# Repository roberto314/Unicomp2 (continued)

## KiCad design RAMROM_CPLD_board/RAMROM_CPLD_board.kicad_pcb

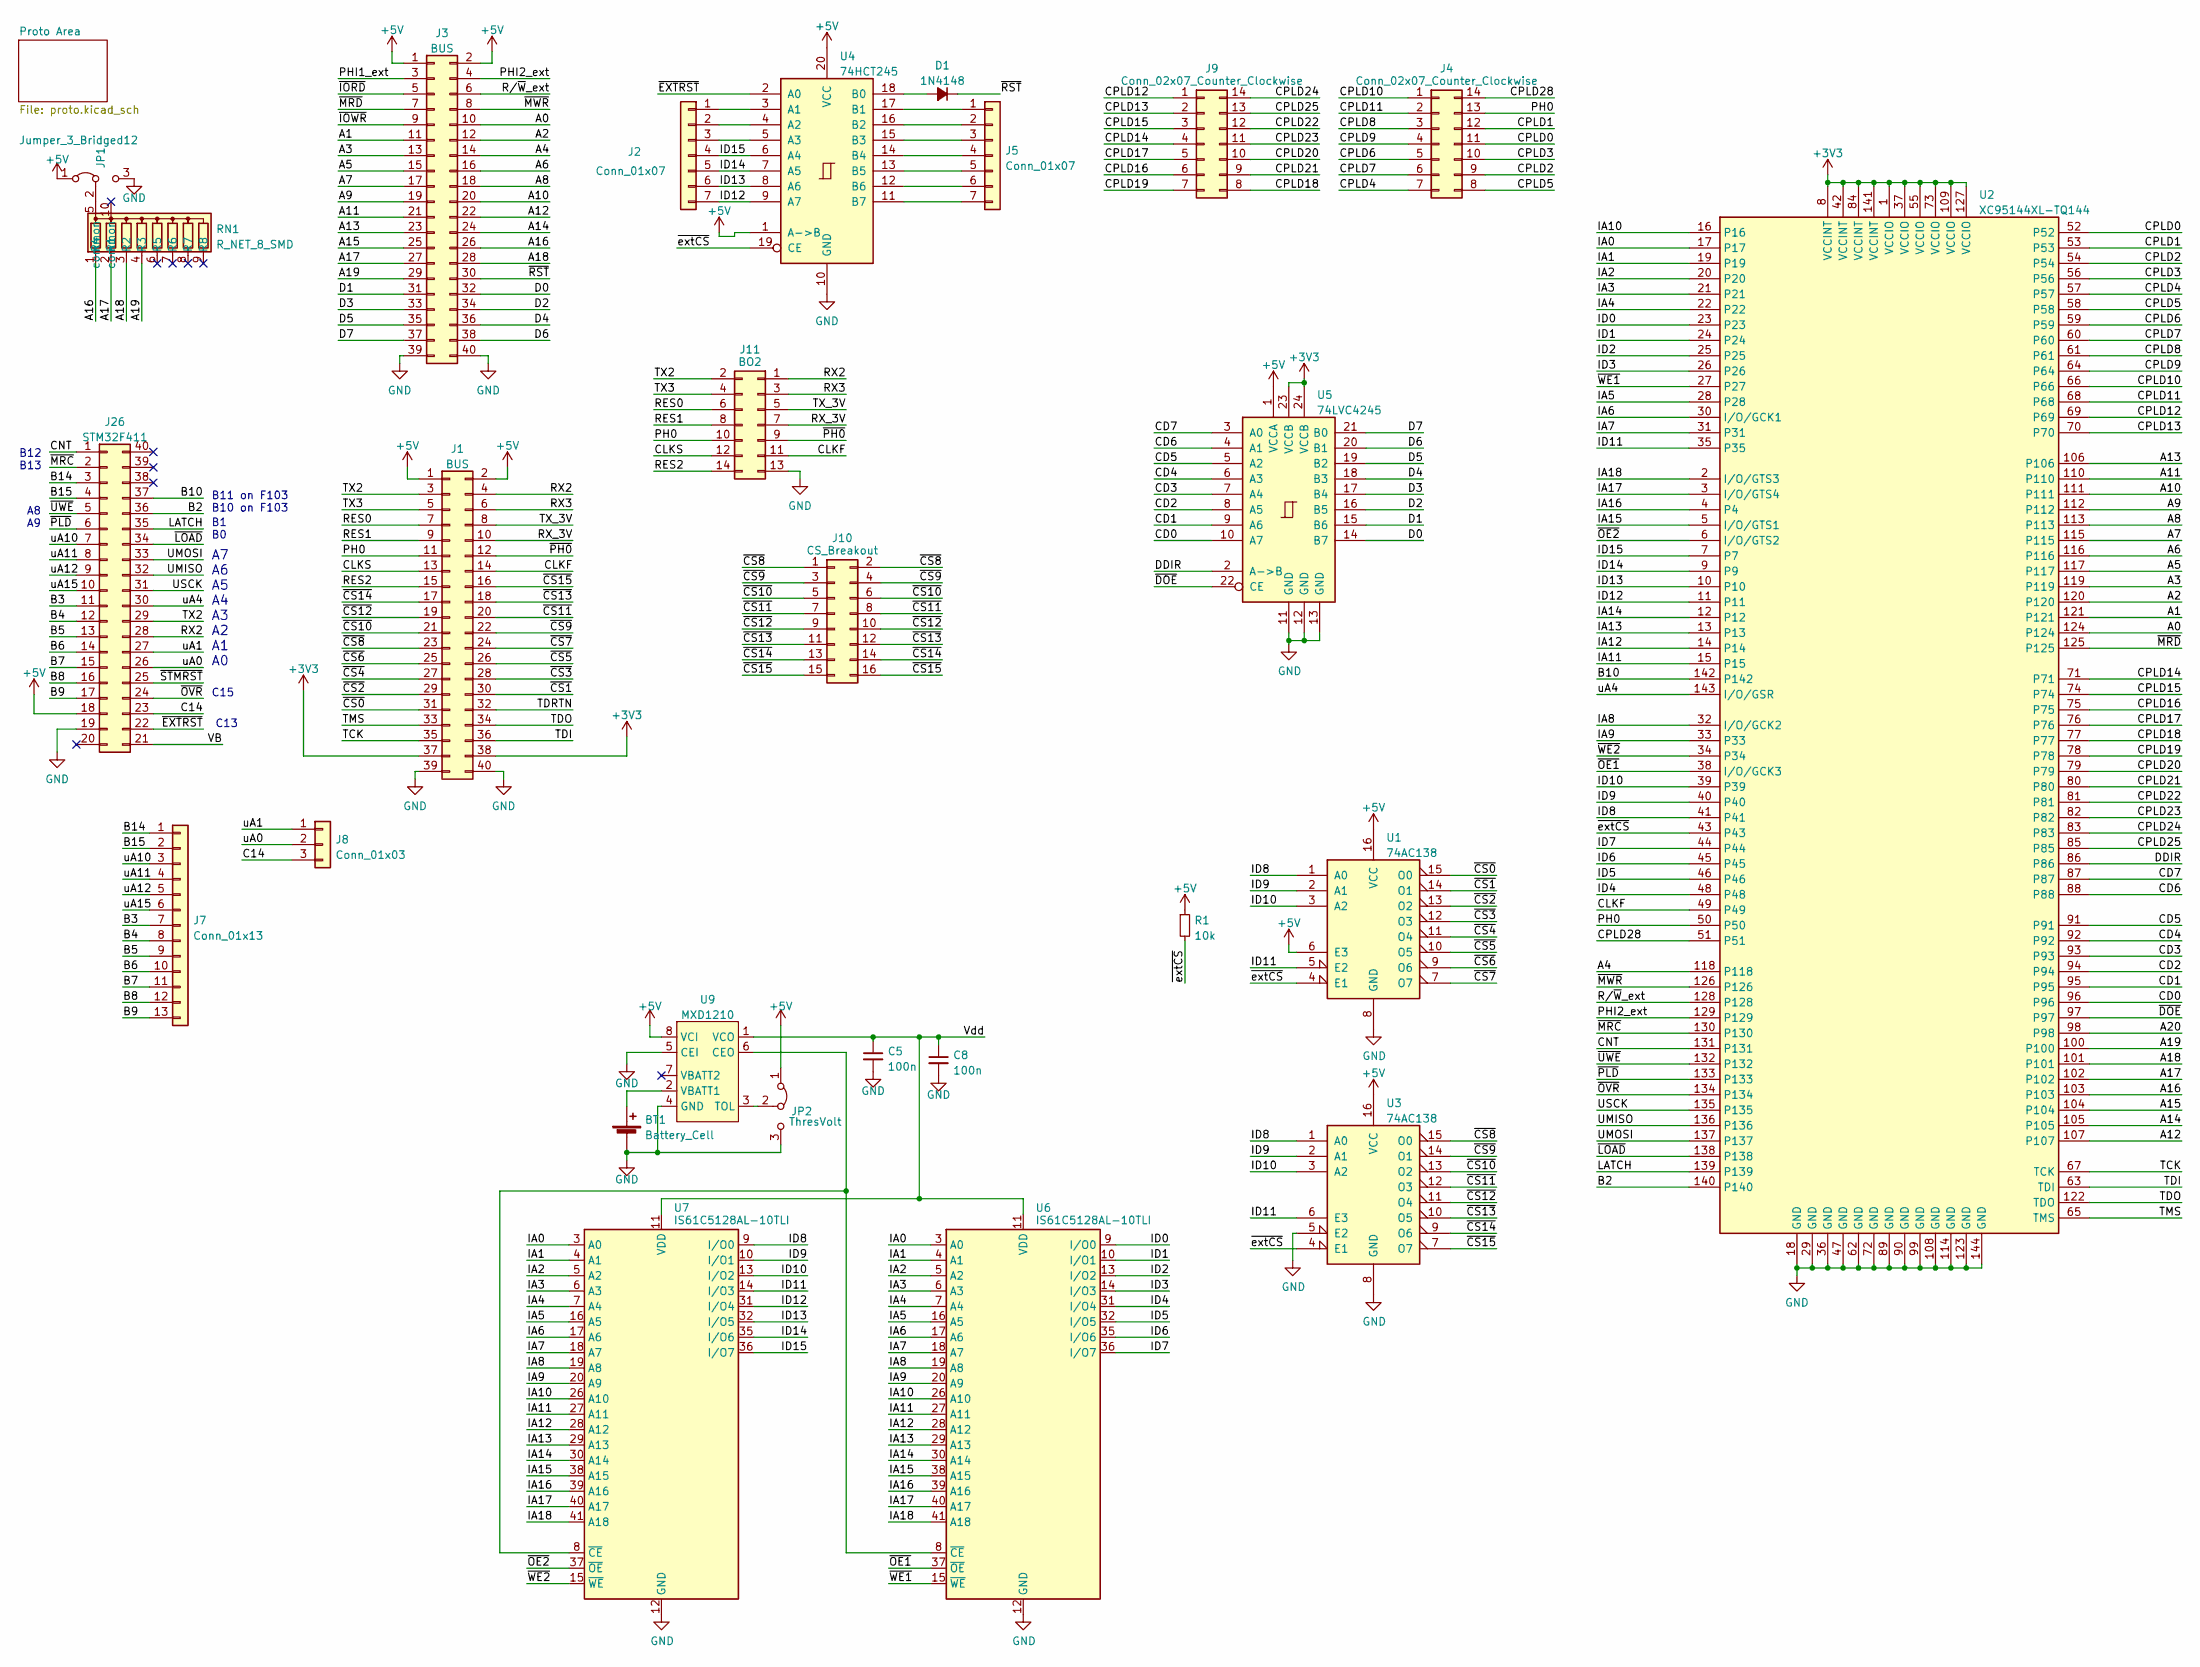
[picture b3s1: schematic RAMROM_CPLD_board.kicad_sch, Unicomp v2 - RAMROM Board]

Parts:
BT1: Battery_Cell; BatteryHolder_Keystone_103_1x20mm
C5, C8: 100n; C_1206_3216Metric
D1: 1N4148; D_1206_3216Metric_Pad1.42x1.75mm_HandSolder
J1, J3: BUS; PinSocket_2x20_P2.54mm_Vertical
J2, J5: Conn_01x07; PinHeader_1x07_P2.54mm_Vertical
J4, J9: Conn_02x07_Counter_Clockwise; PinHeader_2x07_P2.00mm_Vertical
J7: Conn_01x13; PinHeader_1x13_P2.54mm_Vertical
J8: Conn_01x03; PinHeader_1x03_P2.00mm_Vertical
J10: CS_Breakout; PinHeader_2x08_P2.00mm_Vertical
J11: BO2; PinHeader_2x07_P2.54mm_Vertical
J26: STM32F411; DIP-40_W15.24mm_Socket_LongPads
JP1: Jumper_3_Bridged12; SolderJumper-3_P1.3mm_Bridged12_RoundedPad1.0x1.5mm_NumberL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
JP2: ThresVolt; SolderJumper-3_P1.3mm_Bridged12_RoundedPad1.0x1.5mm_NumberL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
R1: 10k; R_1206_3216Metric
RN1: R_NET_8_SMD; R_Net2512_6.4x3.1_P1.27
U1, U3: 74AC138; TSSOP-16_4.4x5mm_P0.65mm
U2: XC95144XL-TQ144; TQFP-144_20x20mm_P0.5mm
U4: 74HCT245; DIP-20_W7.62mm_Socket_LongPads
U5: 74LVC4245; TSSOP-24_4.4x7.8mm_P0.65mm
U6, U7: IS61C5128AL-10TLI; TSOP-II-44_10.16x18.41mm_P0.8mm
U9: MXD1210; SOP-8_3.9x4.9mm_P1.27mm

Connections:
+3V3: J1.37, J1.38, U2.1 (VCCIO), U2.8 (VCCINT), U2.37 (VCCIO), U2.42 (VCCINT), U2.55 (VCCIO), U2.73 (VCCIO), U2.84 (VCCINT), U2.109 (VCCIO), U2.127 (VCCIO), U2.141 (VCCINT), U5.23 (VCCB), U5.24 (VCCB); also elsewhere on the board
+5V: J1.1, J1.2, J3.1, J3.2, J26.18, JP1.1 (A), JP2.1 (A), R1.1, U1.6 (E3), U1.16 (VCC), U3.16 (VCC), U4.1 (A->B), U4.20 (VCC), U5.1 (VCCA), U9.8 (VCI); also elsewhere on the board
/A0: J3.10, U2.124
/A1: J3.11, U2.121
/A2: J3.12, U2.120
/A3: J3.13, U2.119
/A4: J3.14, U2.118
/A5: J3.15, U2.117
/A6: J3.16, U2.116
/A7: J3.17, U2.115
/A8: J3.18, U2.113
/A9: J3.19, U2.112
/A10: J3.20, U2.111
/A11: J3.21, U2.110
/A12: J3.22, U2.107
/A13: J3.23, U2.106
/A14: J3.24, U2.105
/A15: J3.25, U2.104
/A16: J3.26, RN1.1 (R4), U2.103
/A17: J3.27, RN1.2 (R1), U2.102
/A18: J3.28, RN1.3 (R2), U2.101
/A19: J3.29, RN1.4 (R3), U2.100
/A20: U2.98
/B2: J26.36, U2.140
/B3: J7.7, J26.11
/B4: J7.8, J26.12
/B5: J7.9, J26.13
/B6: J7.10, J26.14
/B7: J7.11, J26.15
/B8: J7.12, J26.16
/B9: J7.13, J26.17
/B10: J26.37, U2.142
/B14: J7.1, J26.3
/B15: J7.2, J26.4
/C14: J8.3, J26.23
/CD0: U2.96, U5.10 (A7)
/CD1: U2.95, U5.9 (A6)
/CD2: U2.94, U5.8 (A5)
/CD3: U2.93, U5.7 (A4)
/CD4: U2.92, U5.6 (A3)
/CD5: U2.91, U5.5 (A2)
/CD6: U2.88, U5.4 (A1)
/CD7: U2.87, U5.3 (A0)
/CLKF: J1.14, J11.11, U2.49
/CLKS: J1.13, J11.12
/CNT: J26.1, U2.131
/CPLD0: J4.11, U2.52
/CPLD1: J4.12, U2.53
/CPLD2: J4.9, U2.54
/CPLD3: J4.10, U2.56
/CPLD4: J4.7, U2.57
/CPLD5: J4.8, U2.58
/CPLD6: J4.5, U2.59
/CPLD7: J4.6, U2.60
/CPLD8: J4.3, U2.61
/CPLD9: J4.4, U2.64
/CPLD10: J4.1, U2.66
/CPLD11: J4.2, U2.68
/CPLD12: J9.1, U2.69
/CPLD13: J9.2, U2.70
/CPLD14: J9.4, U2.71
/CPLD15: J9.3, U2.74
/CPLD16: J9.6, U2.75
/CPLD17: J9.5, U2.76
/CPLD18: J9.8, U2.77
/CPLD19: J9.7, U2.78
/CPLD20: J9.10, U2.79
/CPLD21: J9.9, U2.80
/CPLD22: J9.12, U2.81
/CPLD23: J9.11, U2.82
/CPLD24: J9.14, U2.83
/CPLD25: J9.13, U2.85
/CPLD28: J4.14, U2.51
/D0: J3.32, U5.14 (B7)
/D1: J3.31, U5.15 (B6)
/D2: J3.34, U5.16 (B5)
/D3: J3.33, U5.17 (B4)
/D4: J3.36, U5.18 (B3)
/D5: J3.35, U5.19 (B2)
/D6: J3.38, U5.20 (B1)
/D7: J3.37, U5.21 (B0)
/DDIR: U2.86, U5.2 (A->B)
/IA0: U2.17, U6.3 (A0), U7.3 (A0)
/IA1: U2.19, U6.4 (A1), U7.4 (A1)
/IA2: U2.20, U6.5 (A2), U7.5 (A2)
/IA3: U2.21, U6.6 (A3), U7.6 (A3)
/IA4: U2.22, U6.7 (A4), U7.7 (A4)
/IA5: U2.28, U6.16 (A5), U7.16 (A5)
/IA6: U2.30 (I/O/GCK1), U6.17 (A6), U7.17 (A6)
/IA7: U2.31, U6.18 (A7), U7.18 (A7)
/IA8: U2.32 (I/O/GCK2), U6.19 (A8), U7.19 (A8)
/IA9: U2.33, U6.20 (A9), U7.20 (A9)
/IA10: U2.16, U6.26 (A10), U7.26 (A10)
/IA11: U2.15, U6.27 (A11), U7.27 (A11)
/IA12: U2.14, U6.28 (A12), U7.28 (A12)
/IA13: U2.13, U6.29 (A13), U7.29 (A13)
/IA14: U2.12, U6.30 (A14), U7.30 (A14)
/IA15: U2.5 (I/O/GTS1), U6.38 (A15), U7.38 (A15)
/IA16: U2.4, U6.39 (A16), U7.39 (A16)
/IA17: U2.3 (I/O/GTS4), U6.40 (A17), U7.40 (A17)
/IA18: U2.2 (I/O/GTS3), U6.41 (A18), U7.41 (A18)
/ID0: U2.23, U6.9 (I/O0)
/ID1: U2.24, U6.10 (I/O1)
/ID2: U2.25, U6.13 (I/O2)
/ID3: U2.26, U6.14 (I/O3)
/ID4: U2.48, U6.31 (I/O4)
/ID5: U2.46, U6.32 (I/O5)
/ID6: U2.45, U6.35 (I/O6)
/ID7: U2.44, U6.36 (I/O7)
/ID8: U1.1 (A0), U2.41, U3.1 (A0), U7.9 (I/O0)
/ID9: U1.2 (A1), U2.40, U3.2 (A1), U7.10 (I/O1)
/ID10: U1.3 (A2), U2.39, U3.3 (A2), U7.13 (I/O2)
/ID11: U1.5 (E2), U2.35, U3.6 (E3), U7.14 (I/O3)
/ID12: J2.7, U2.11, U4.9 (A7), U7.31 (I/O4)
/ID13: J2.6, U2.10, U4.8 (A6), U7.32 (I/O5)
/ID14: J2.5, U2.9, U4.7 (A5), U7.35 (I/O6)
/ID15: J2.4, U2.7, U4.6 (A4), U7.36 (I/O7)
/LATCH: J26.35, U2.139
/PH0: J1.11, J4.13, J11.10, U2.50
/PHI1_ext: J3.3
/PHI2_ext: J3.4, U2.129
/RES0: J1.7, J11.6
/RES1: J1.9, J11.8
/RES2: J1.15, J11.14
/RX2: J1.4, J11.1, J26.28
/RX3: J1.6, J11.3
/RX_3V: J1.10, J11.7
/R/~W_ext: J3.6, U2.128
/TCK: J1.35, U2.67 (TCK)
/TDI: J1.36, U2.63 (TDI)
/TDO: J1.34, U2.122 (TDO)
/TDRTN: J1.32
/TMS: J1.33, U2.65 (TMS)
/TX2: J1.3, J11.2, J26.29
/TX3: J1.5, J11.4
/TX_3V: J1.8, J11.5
/UMISO: J26.32, U2.136
/UMOSI: J26.33, U2.137
/USCK: J26.31, U2.135
/VB: J26.21
/Vdd: C5.1, C8.1, U6.11 (VDD), U6.33 (VDD), U7.11 (VDD), U7.33 (VDD), U9.1 (VCO)
/uA0: J8.2, J26.26
/uA1: J8.1, J26.27
/uA4: J26.30, U2.143 (I/O/GSR)
/uA10: J7.3, J26.7
/uA11: J7.4, J26.8
/uA12: J7.5, J26.9
/uA15: J7.6, J26.10
/~CS0: J1.31, U1.15 (O0)
/~CS1: J1.30, U1.14 (O1)
/~CS2: J1.29, U1.13 (O2)
/~CS3: J1.28, U1.12 (O3)
/~CS4: J1.27, U1.11 (O4)
/~CS5: J1.26, U1.10 (O5)
/~CS6: J1.25, U1.9 (O6)
/~CS7: J1.24, U1.7 (O7)
/~CS8: J1.23, J10.1, J10.2, U3.15 (O0)
/~CS9: J1.22, J10.3, J10.4, U3.14 (O1)
/~CS10: J1.21, J10.5, J10.6, U3.13 (O2)
/~CS11: J1.20, J10.7, J10.8, U3.12 (O3)
/~CS12: J1.19, J10.9, J10.10, U3.11 (O4)
/~CS13: J1.18, J10.11, J10.12, U3.10 (O5)
/~CS14: J1.17, J10.13, J10.14, U3.9 (O6)
/~CS15: J1.16, J10.15, J10.16, U3.7 (O7)
/~DOE: U2.97, U5.22 (CE)
/~EXTRST: J26.22, U4.2 (A0)
/~IORD: J3.5
/~IOWR: J3.9
/~LOAD: J26.34, U2.138
/~MRC: J26.2, U2.130
/~MRD: J3.7, U2.125
/~MWR: J3.8, U2.126
/~OE1: U2.38 (I/O/GCK3), U6.37 (~OE)
/~OE2: U2.6 (I/O/GTS2), U7.37 (~OE)
/~OVR: J26.24, U2.134
/~PH0: J1.12, J11.9
/~PLD: J26.6, U2.133
/~RST: D1.1 (K), J3.30
/~STMRST: J26.25
/~UWE: J26.5, U2.132
/~WE1: U2.27, U6.15 (~WE)
/~WE2: U2.34, U7.15 (~WE)
/~extCS: R1.2, U1.4 (E1), U2.43, U3.4 (E1), U4.19 (CE)
GND: BT1.2 (-), C5.2, C8.2, J1.39, J1.40, J3.39, J3.40, J11.13, J26.19, JP1.3 (B), JP2.3 (B), U1.8 (GND), U2.18 (GND), U2.29 (GND), U2.36 (GND), U2.47 (GND), U2.62 (GND), U2.72 (GND), U2.89 (GND), U2.90 (GND), U2.99 (GND), U2.108 (GND), U2.114 (GND), U2.123 (GND), U2.144 (GND), U3.5 (E2), U3.8 (GND), U4.10 (GND), U5.11 (GND), U5.12 (GND), U5.13 (GND), U6.12 (GND), U6.34 (GND), U7.12 (GND), U7.34 (GND), U9.4 (GND), U9.5 (CEI); also elsewhere on the board
unnamed: BT1.1 (+), U9.2 (VBATT1)
unnamed: D1.2 (A), U4.18 (B0)
unnamed: J2.1, U4.3 (A1)
unnamed: J2.2, U4.4 (A2)
unnamed: J2.3, U4.5 (A3)
unnamed: J5.1, U4.17 (B1)
unnamed: J5.2, U4.16 (B2)
unnamed: J5.3, U4.15 (B3)
unnamed: J5.4, U4.14 (B4)
unnamed: J5.5, U4.13 (B5)
unnamed: J5.6, U4.12 (B6)
unnamed: J5.7, U4.11 (B7)
unnamed: JP1.2 (C), RN1.5 (common)
unnamed: JP2.2 (C), U9.3 (TOL)
unnamed: U6.8 (~CE), U7.8 (~CE), U9.6 (CEO)

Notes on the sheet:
C13
B11 on F103 B10 on F103
B12 B13
C15
A7 A6 A5 A4 A3 A2 A1 A0
B1 B0
A8 A9

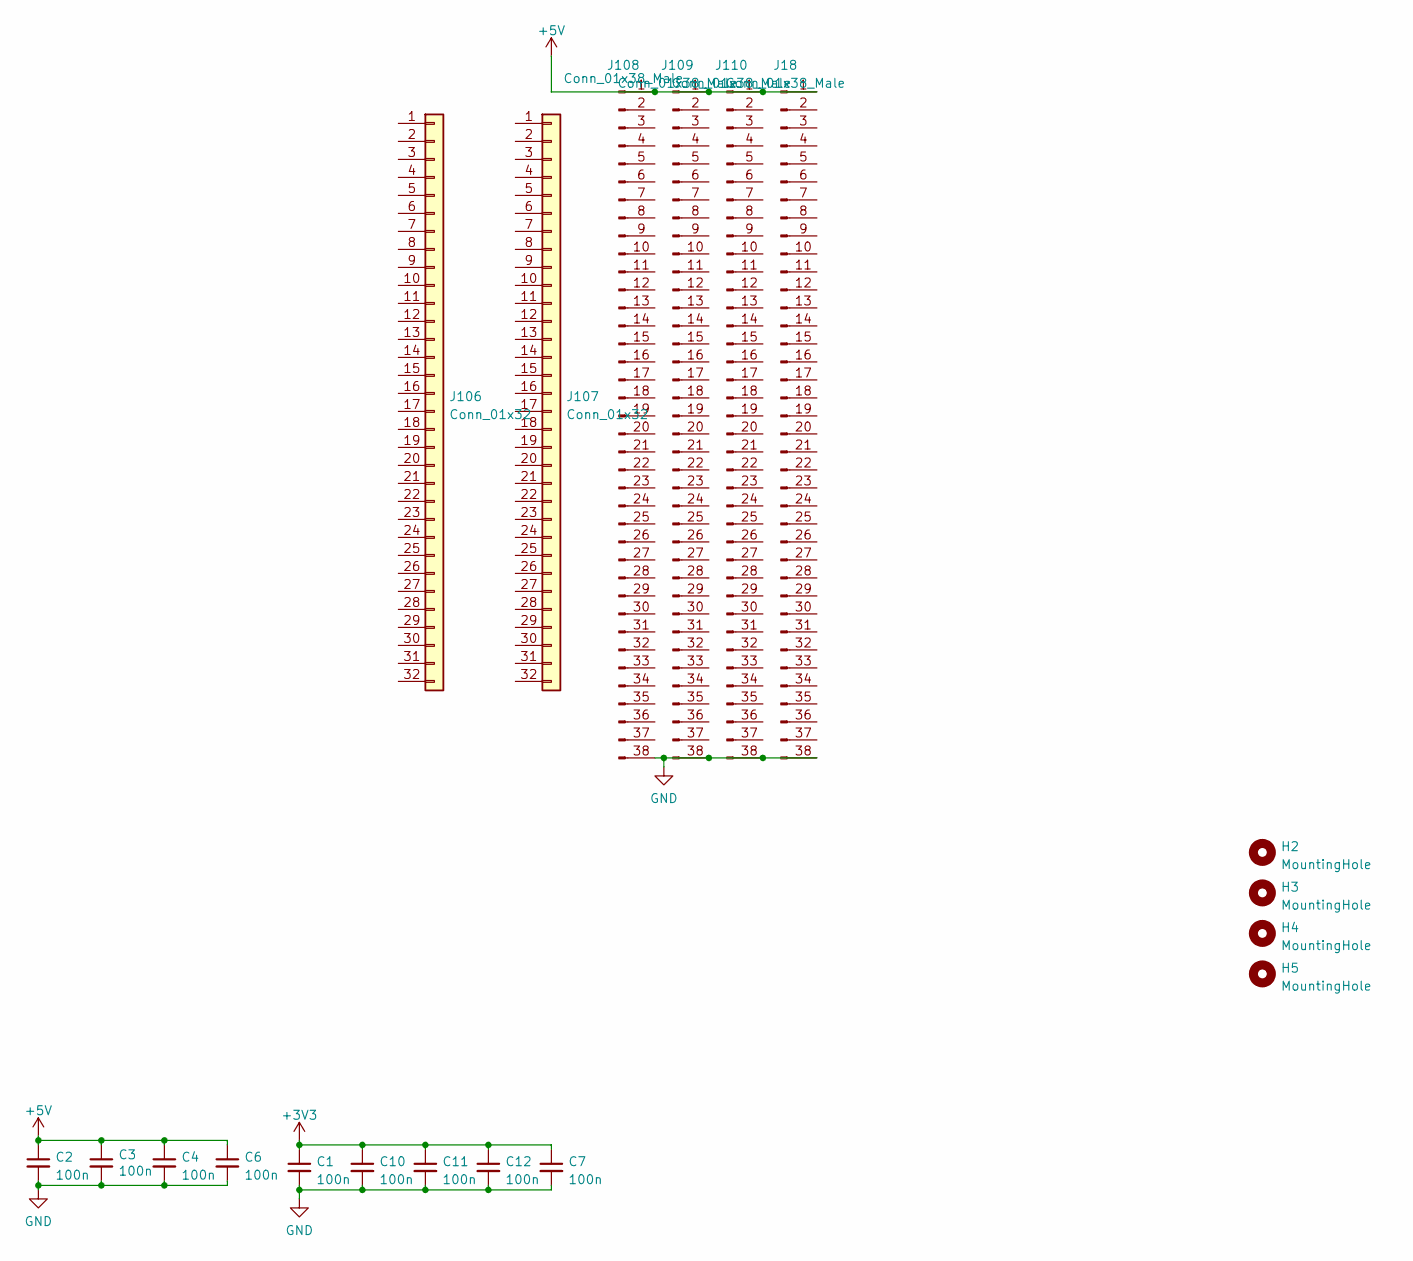
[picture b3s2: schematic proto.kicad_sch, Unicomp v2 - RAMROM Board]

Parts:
C1, C2, C4, C6, C7, C10, C11, C12: 100n; C_1206_3216Metric
C3: 100n; C_1206_3216Metric_Pad1.33x1.80mm_HandSolder
H2, H3, H4, H5: MountingHole; MountingHole_3.2mm_M3
J18, J108, J109, J110: Conn_01x38_Male; PinHeader_1x38_P2.54mm_Vertical
J106, J107: Conn_01x32; PinHeader_1x32_P2.54mm_Vertical

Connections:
+3V3: C1.1, C7.1, C10.1, C11.1, C12.1; also elsewhere on the board
+5V: C2.1, C3.1, C4.1, C6.1, J18.1, J108.1, J109.1, J110.1; also elsewhere on the board
GND: C1.2, C2.2, C3.2, C4.2, C6.2, C7.2, C10.2, C11.2, C12.2, J18.38, J108.38, J109.38, J110.38; also elsewhere on the board

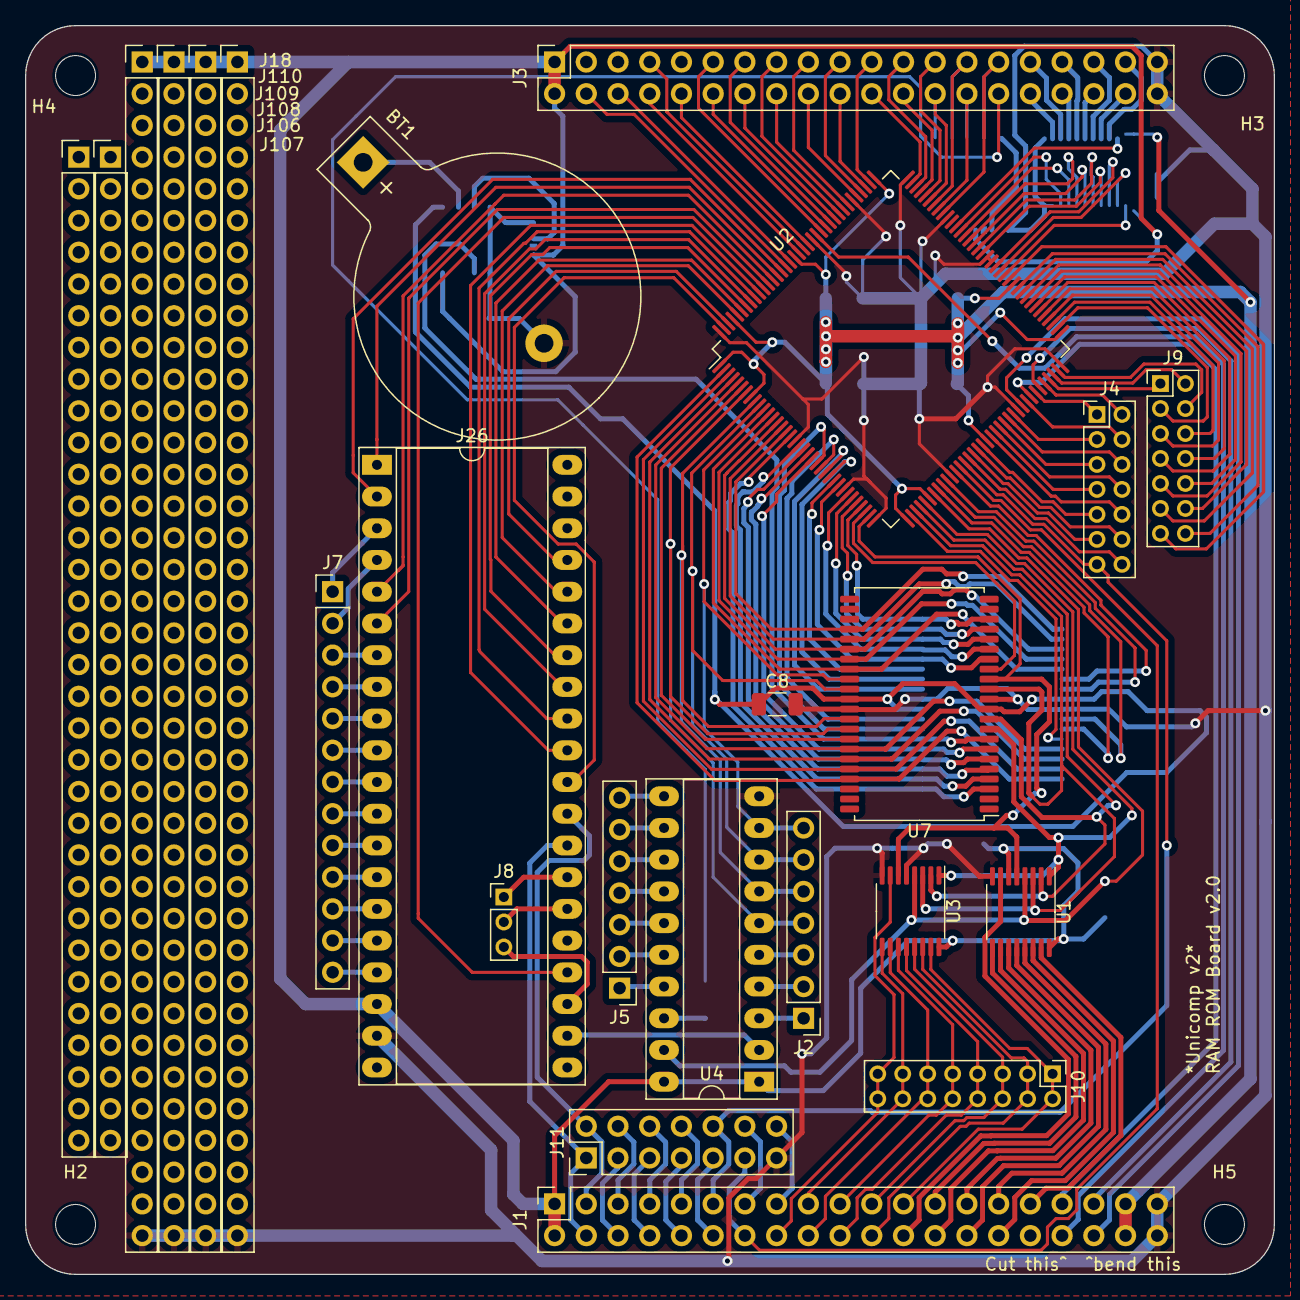
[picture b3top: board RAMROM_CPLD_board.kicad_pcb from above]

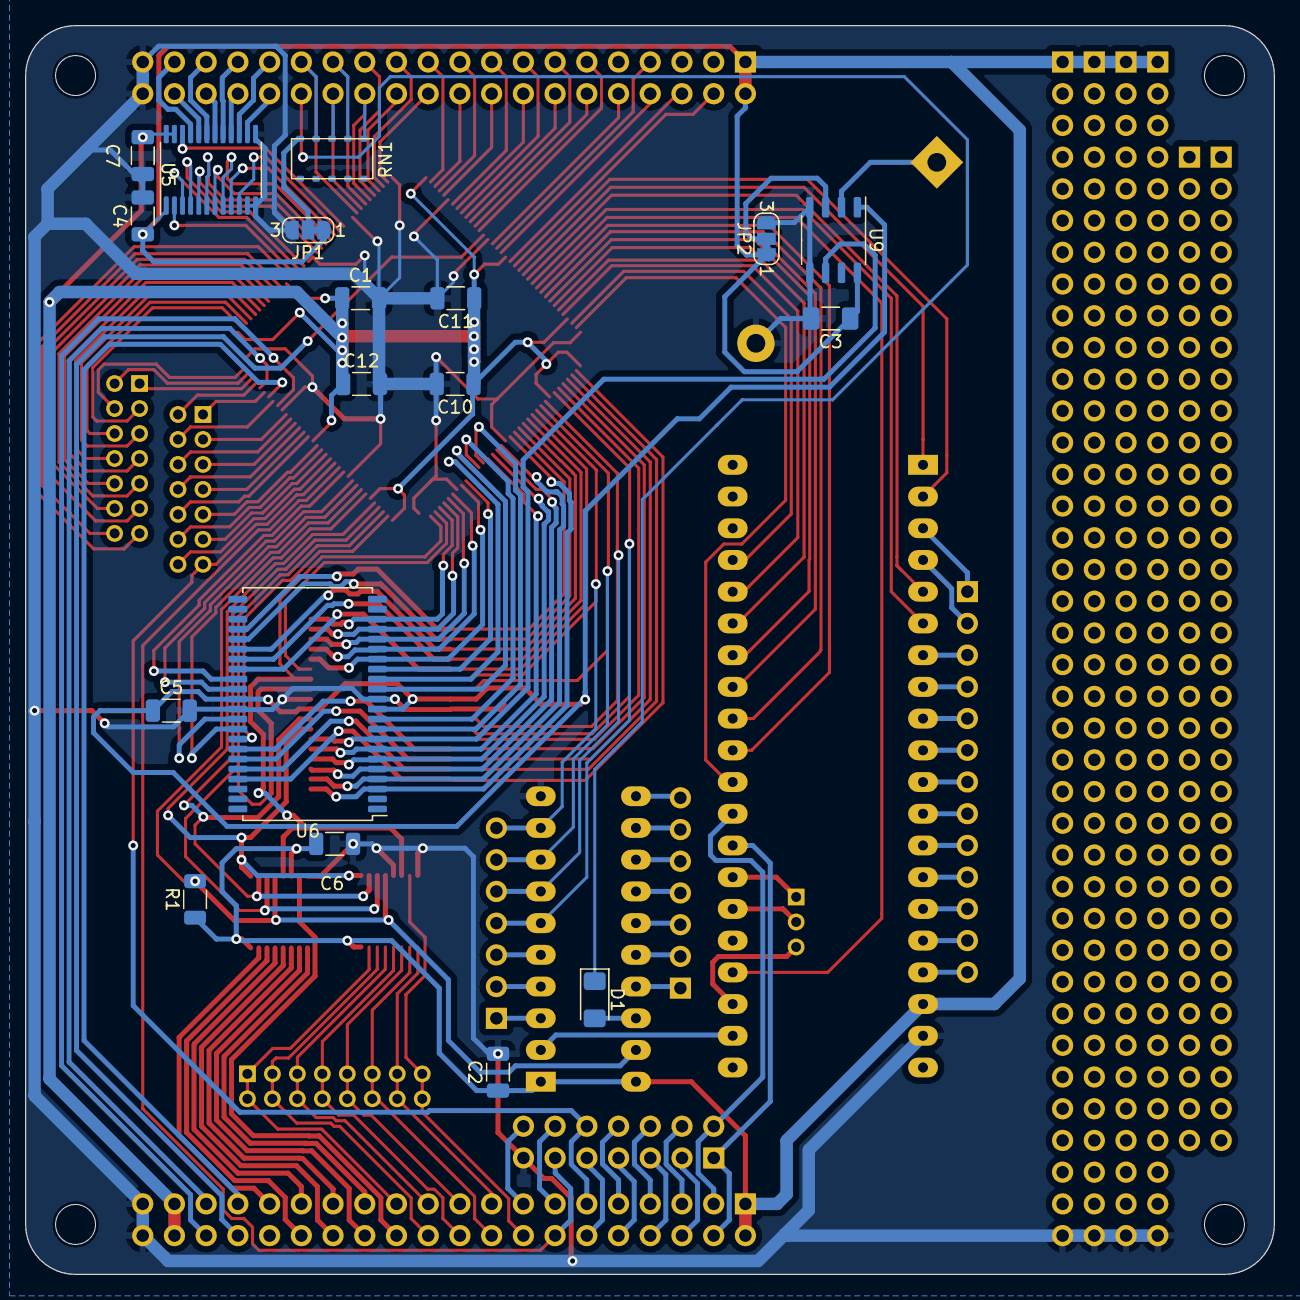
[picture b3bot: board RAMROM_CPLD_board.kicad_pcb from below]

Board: 2 copper layers, 100.0 x 100.0 mm, 46 parts (18 on the bottom side), 192 nets.

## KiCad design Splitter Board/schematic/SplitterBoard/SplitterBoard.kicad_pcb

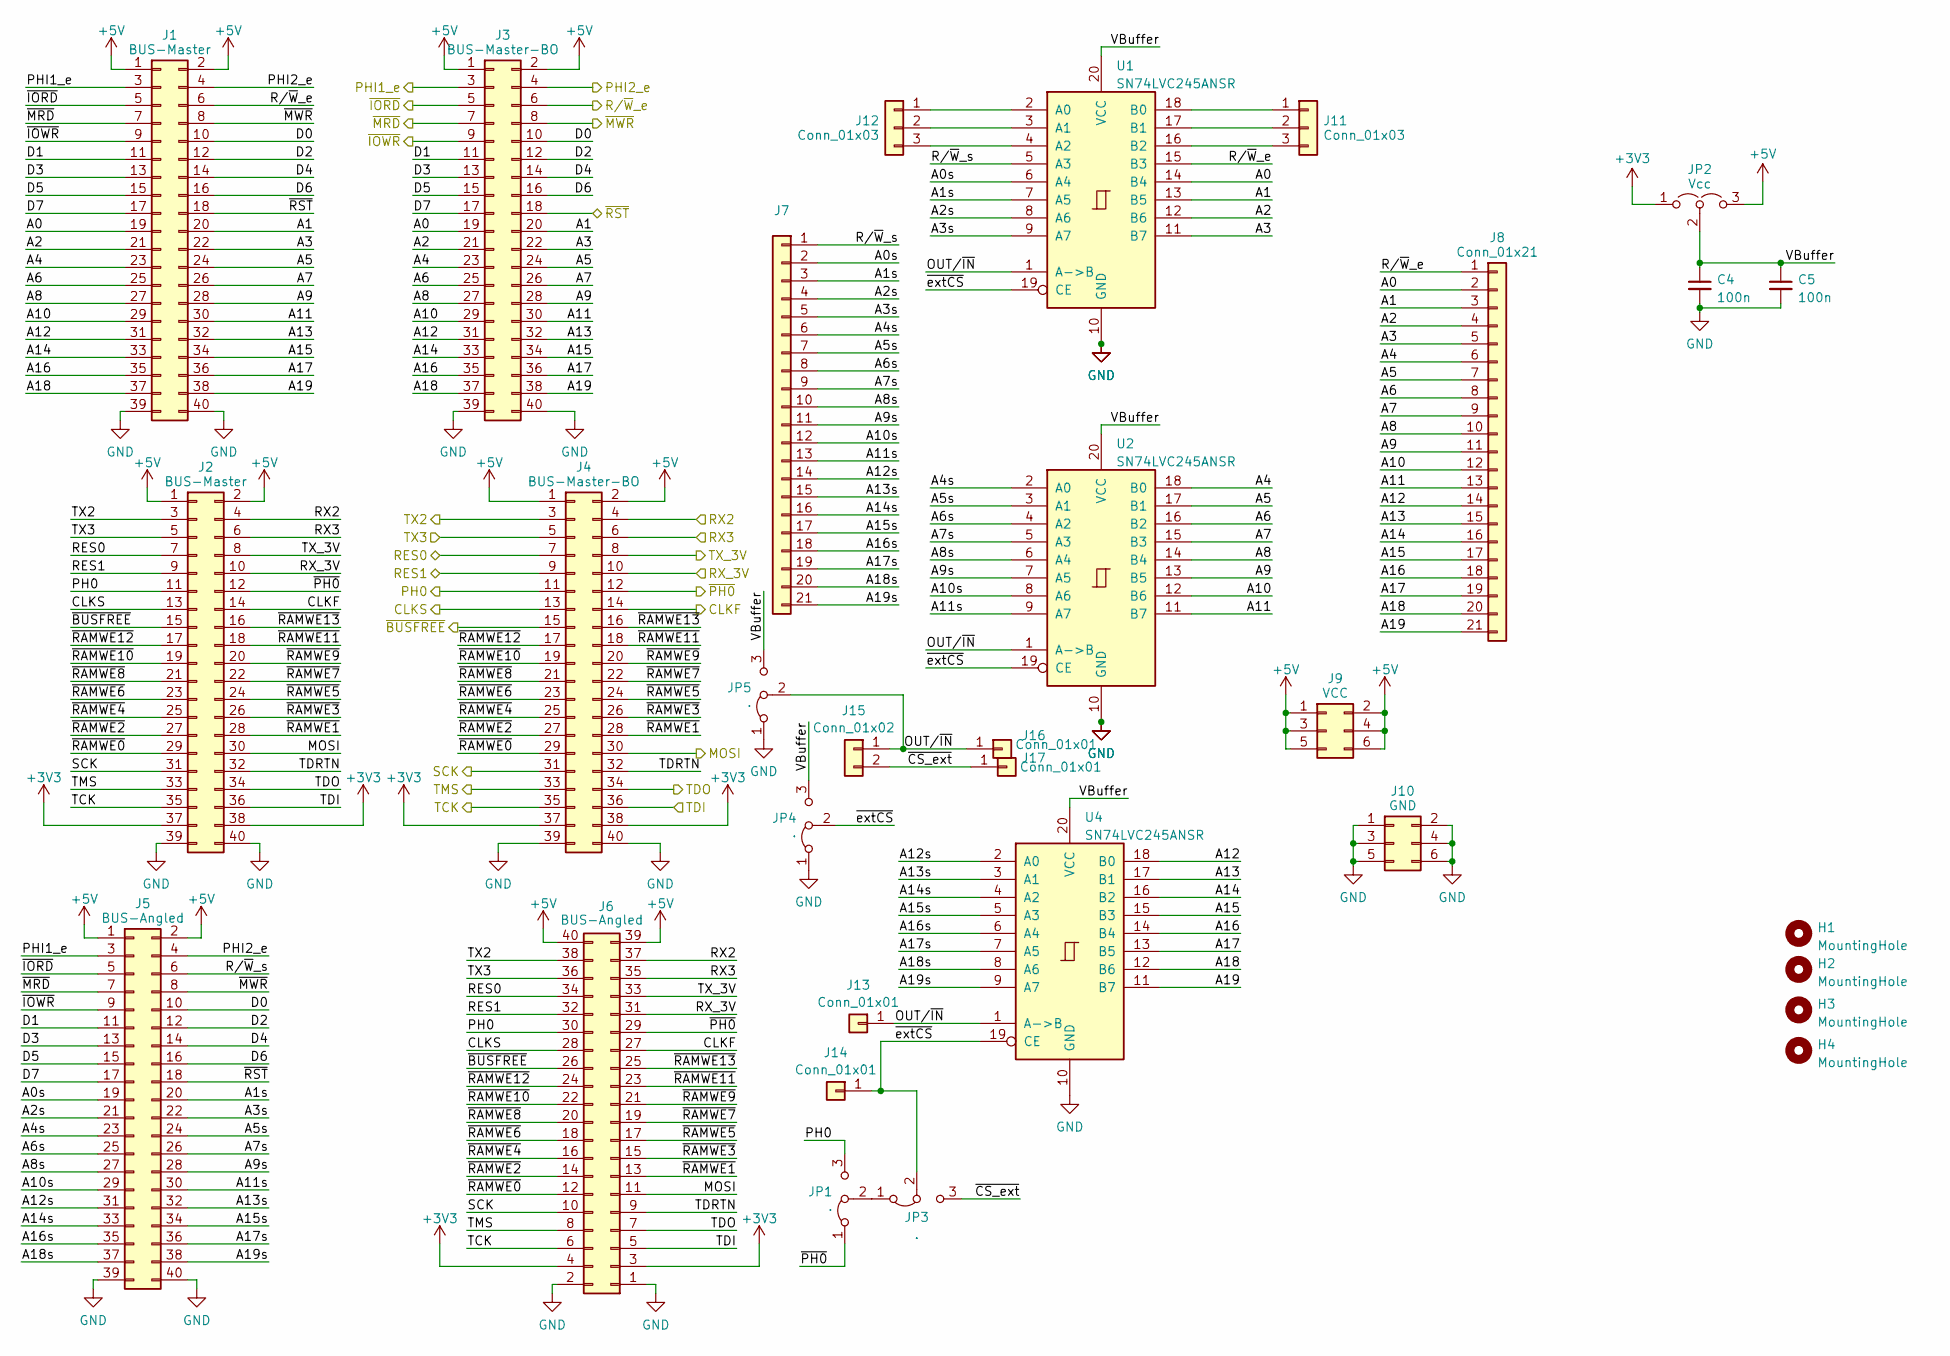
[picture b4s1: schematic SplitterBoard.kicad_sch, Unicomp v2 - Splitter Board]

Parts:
C4, C5: 100n; C_1206_3216Metric
H1, H2, H3, H4: MountingHole; MountingHole_3.2mm_M3
J1, J2: BUS-Master; PinSocket_2x20_P2.54mm_Vertical
J3, J4: BUS-Master-BO; PinSocket_2x20_P2.54mm_Vertical
J5, J6: BUS-Angled; PinHeader_2x20_P2.54mm_Horizontal
J7, J8: Conn_01x21; PinHeader_1x21_P2.54mm_Vertical
J9: VCC; PinHeader_2x03_P2.54mm_Vertical
J10: GND; PinHeader_2x03_P2.54mm_Vertical
J11, J12: Conn_01x03; PinHeader_1x03_P2.54mm_Vertical
J13, J14, J16, J17: Conn_01x01; PinHeader_1x01_P2.00mm_Vertical
J15: Conn_01x02; PinHeader_1x02_P2.54mm_Vertical
JP1, JP3, JP4, JP5: .; SolderJumper-3_P1.3mm_Open_Pad1.0x1.5mm_NumberLabels
JP2: Vcc; SolderJumper-3_P1.3mm_Open_RoundedPad1.0x1.5mm_NumberLabels
U1, U2, U4: SN74LVC245ANSR; SO-20_5.3x12.6mm_P1.27mm

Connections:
+3V3: J2.37, J2.38, J4.37, J4.38, J6.3, J6.4, JP2.1 (A)
+5V: J1.1, J1.2, J2.1, J2.2, J3.1, J3.2, J4.1, J4.2, J5.1, J5.2, J6.39, J6.40, J9.1, J9.2, J9.3, J9.4, J9.5, J9.6, JP2.3 (B)
/A0: J1.19, J3.19, J8.2, U1.14 (B4)
/A0s: J5.19, J7.2, U1.6 (A4)
/A1: J1.20, J3.20, J8.3, U1.13 (B5)
/A1s: J5.20, J7.3, U1.7 (A5)
/A2: J1.21, J3.21, J8.4, U1.12 (B6)
/A2s: J5.21, J7.4, U1.8 (A6)
/A3: J1.22, J3.22, J8.5, U1.11 (B7)
/A3s: J5.22, J7.5, U1.9 (A7)
/A4: J1.23, J3.23, J8.6, U2.18 (B0)
/A4s: J5.23, J7.6, U2.2 (A0)
/A5: J1.24, J3.24, J8.7, U2.17 (B1)
/A5s: J5.24, J7.7, U2.3 (A1)
/A6: J1.25, J3.25, J8.8, U2.16 (B2)
/A6s: J5.25, J7.8, U2.4 (A2)
/A7: J1.26, J3.26, J8.9, U2.15 (B3)
/A7s: J5.26, J7.9, U2.5 (A3)
/A8: J1.27, J3.27, J8.10, U2.14 (B4)
/A8s: J5.27, J7.10, U2.6 (A4)
/A9: J1.28, J3.28, J8.11, U2.13 (B5)
/A9s: J5.28, J7.11, U2.7 (A5)
/A10: J1.29, J3.29, J8.12, U2.12 (B6)
/A10s: J5.29, J7.12, U2.8 (A6)
/A11: J1.30, J3.30, J8.13, U2.11 (B7)
/A11s: J5.30, J7.13, U2.9 (A7)
/A12: J1.31, J3.31, J8.14, U4.18 (B0)
/A12s: J5.31, J7.14, U4.2 (A0)
/A13: J1.32, J3.32, J8.15, U4.17 (B1)
/A13s: J5.32, J7.15, U4.3 (A1)
/A14: J1.33, J3.33, J8.16, U4.16 (B2)
/A14s: J5.33, J7.16, U4.4 (A2)
/A15: J1.34, J3.34, J8.17, U4.15 (B3)
/A15s: J5.34, J7.17, U4.5 (A3)
/A16: J1.35, J3.35, J8.18, U4.14 (B4)
/A16s: J5.35, J7.18, U4.6 (A4)
/A17: J1.36, J3.36, J8.19, U4.13 (B5)
/A17s: J5.36, J7.19, U4.7 (A5)
/A18: J1.37, J3.37, J8.20, U4.12 (B6)
/A18s: J5.37, J7.20, U4.8 (A6)
/A19: J1.38, J3.38, J8.21, U4.11 (B7)
/A19s: J5.38, J7.21, U4.9 (A7)
/CLKF: J2.14, J4.14, J6.27
/CLKS: J2.13, J4.13, J6.28
/D0: J1.10, J3.10, J5.10
/D1: J1.11, J3.11, J5.11
/D2: J1.12, J3.12, J5.12
/D3: J1.13, J3.13, J5.13
/D4: J1.14, J3.14, J5.14
/D5: J1.15, J3.15, J5.15
/D6: J1.16, J3.16, J5.16
/D7: J1.17, J3.17, J5.17
/MOSI: J2.30, J4.30, J6.11
/OUT/~IN: J13.1, J15.1, J16.1, JP5.2 (C), U1.1 (A->B), U2.1 (A->B), U4.1 (A->B)
/PH0: J2.11, J4.11, J6.30, JP1.3 (B)
/PHI1_e: J1.3, J3.3, J5.3
/PHI2_e: J1.4, J3.4, J5.4
/RES0: J2.7, J4.7, J6.34
/RES1: J2.9, J4.9, J6.32
/RX2: J2.4, J4.4, J6.37
/RX3: J2.6, J4.6, J6.35
/RX_3V: J2.10, J4.10, J6.31
/R/~W_e: J1.6, J3.6, J8.1, U1.15 (B3)
/R/~W_s: J5.6, J7.1, U1.5 (A3)
/SCK: J2.31, J4.31, J6.10
/TCK: J2.35, J4.35, J6.6
/TDI: J2.36, J4.36, J6.5
/TDO: J2.34, J4.34, J6.7
/TDRTN: J2.32, J4.32, J6.9
/TMS: J2.33, J4.33, J6.8
/TX2: J2.3, J4.3, J6.38
/TX3: J2.5, J4.5, J6.36
/TX_3V: J2.8, J4.8, J6.33
/VBuffer: C4.1, C5.1, JP2.2 (C), JP4.3 (B), JP5.3 (B), U1.20 (VCC), U2.20 (VCC), U4.20 (VCC)
/~BUSFREE: J2.15, J4.15, J6.26
/~CS_ext: J15.2, J17.1, JP3.3 (B)
/~IORD: J1.5, J3.5, J5.5
/~IOWR: J1.9, J3.9, J5.9
/~MRD: J1.7, J3.7, J5.7
/~MWR: J1.8, J3.8, J5.8
/~PH0: J2.12, J4.12, J6.29, JP1.1 (A)
/~RAMWE0: J2.29, J4.29, J6.12
/~RAMWE1: J2.28, J4.28, J6.13
/~RAMWE2: J2.27, J4.27, J6.14
/~RAMWE3: J2.26, J4.26, J6.15
/~RAMWE4: J2.25, J4.25, J6.16
/~RAMWE5: J2.24, J4.24, J6.17
/~RAMWE6: J2.23, J4.23, J6.18
/~RAMWE7: J2.22, J4.22, J6.19
/~RAMWE8: J2.21, J4.21, J6.20
/~RAMWE9: J2.20, J4.20, J6.21
/~RAMWE10: J2.19, J4.19, J6.22
/~RAMWE11: J2.18, J4.18, J6.23
/~RAMWE12: J2.17, J4.17, J6.24
/~RAMWE13: J2.16, J4.16, J6.25
/~RST: J1.18, J3.18, J5.18
/~extCS: J14.1, JP3.2 (C), JP4.2 (C), U1.19 (CE), U2.19 (CE), U4.19 (CE)
GND: C4.2, C5.2, J1.39, J1.40, J2.39, J2.40, J3.39, J3.40, J4.39, J4.40, J5.39, J5.40, J6.1, J6.2, J10.1, J10.2, J10.3, J10.4, J10.5, J10.6, JP4.1 (A), JP5.1 (A), U1.10 (GND), U2.10 (GND), U4.10 (GND)
unnamed: J11.1, U1.18 (B0)
unnamed: J11.2, U1.17 (B1)
unnamed: J11.3, U1.16 (B2)
unnamed: J12.1, U1.2 (A0)
unnamed: J12.2, U1.3 (A1)
unnamed: J12.3, U1.4 (A2)
unnamed: JP1.2 (C), JP3.1 (A)

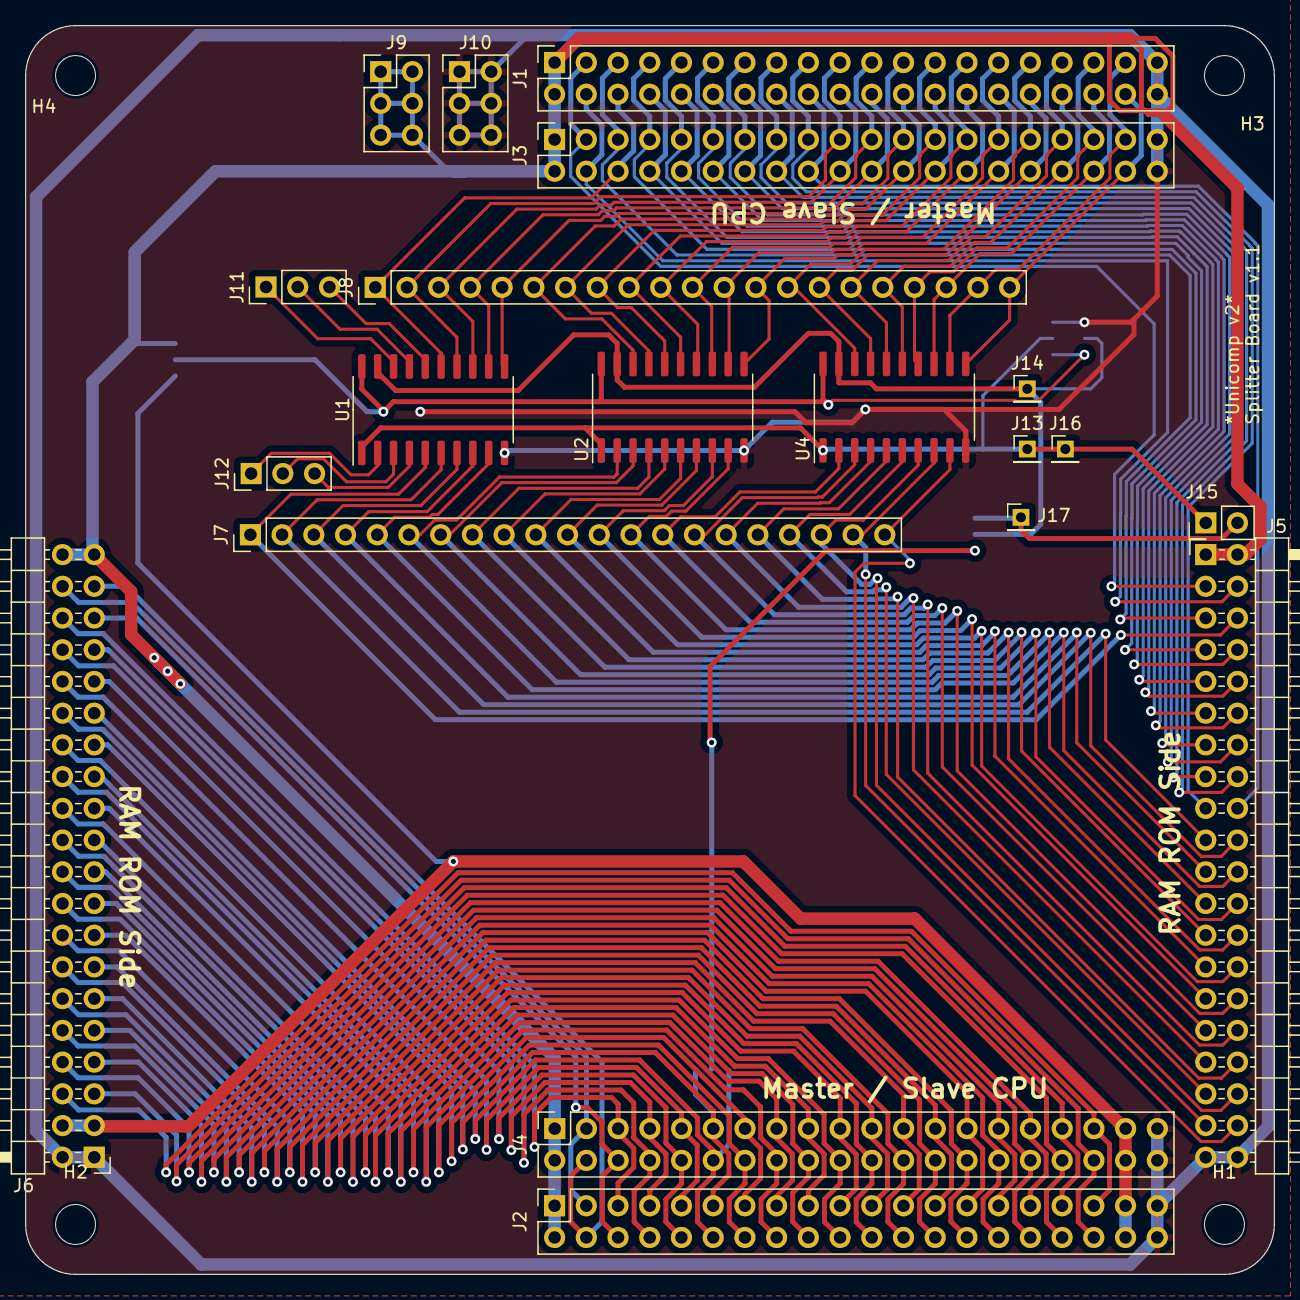
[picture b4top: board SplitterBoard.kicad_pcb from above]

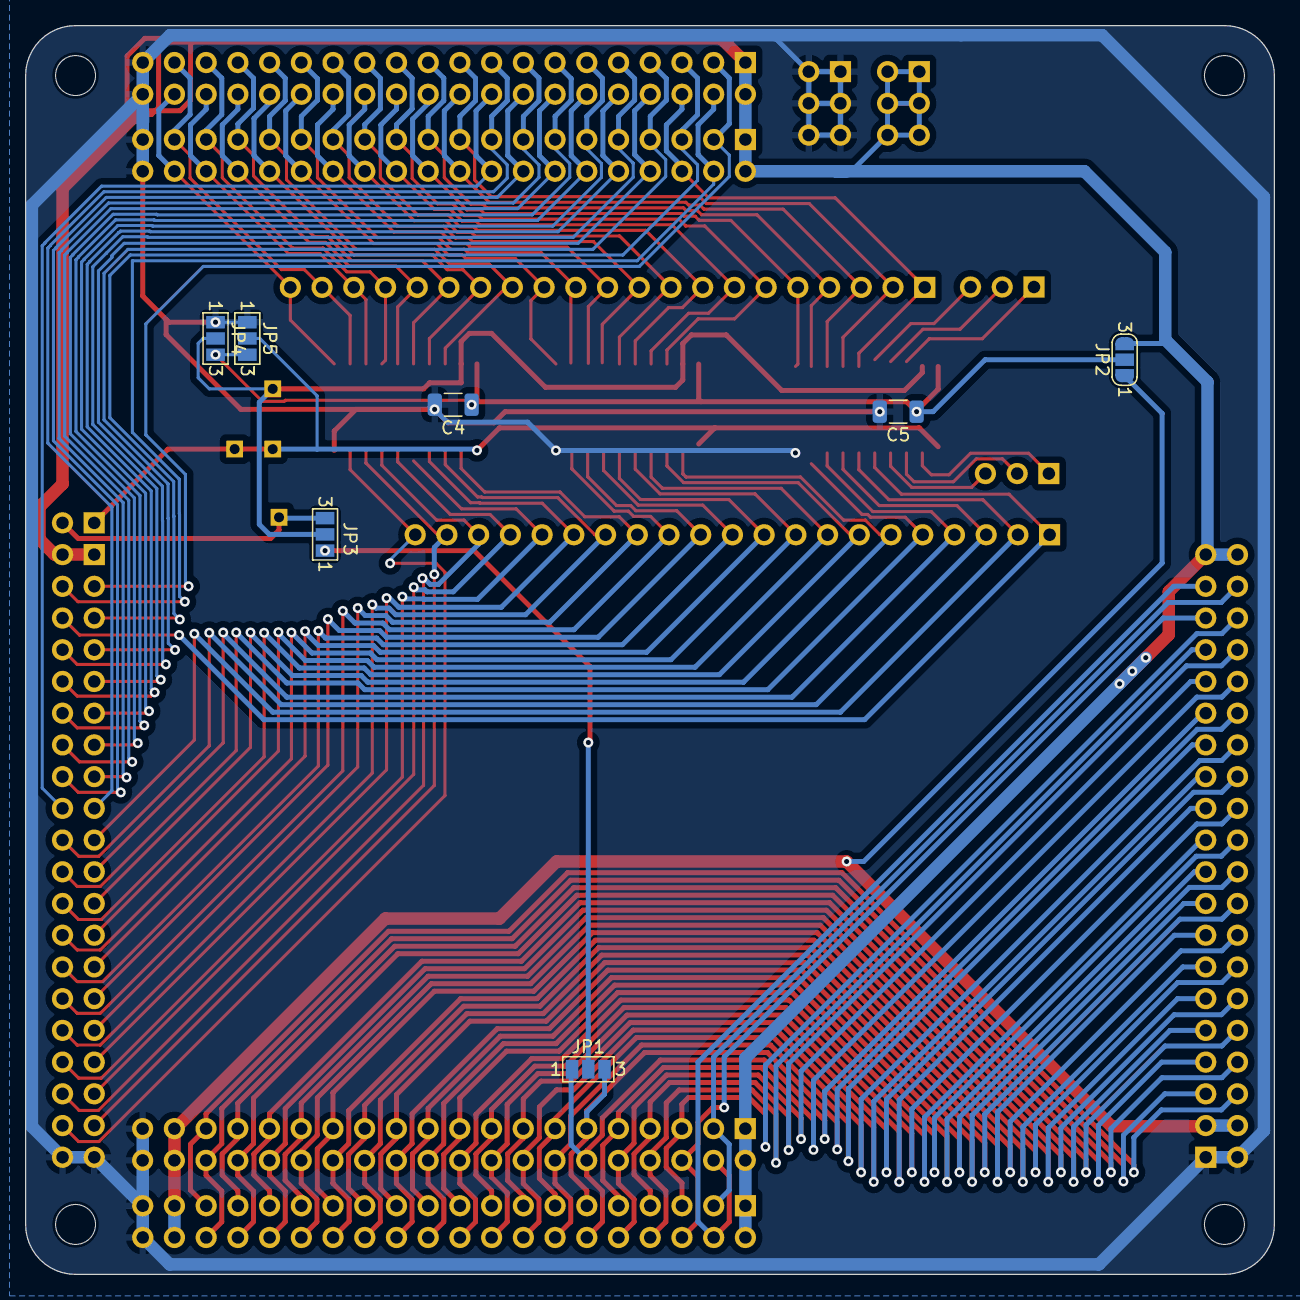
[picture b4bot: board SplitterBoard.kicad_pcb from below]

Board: 2 copper layers, 100.0 x 100.0 mm, 31 parts (7 on the bottom side), 105 nets.
